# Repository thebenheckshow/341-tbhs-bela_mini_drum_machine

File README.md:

# 341-tbhs-bela_mini_drum_machine
In this episode Felix creates a drum machine with the Pocket Beagle and Bela Mini!!!!

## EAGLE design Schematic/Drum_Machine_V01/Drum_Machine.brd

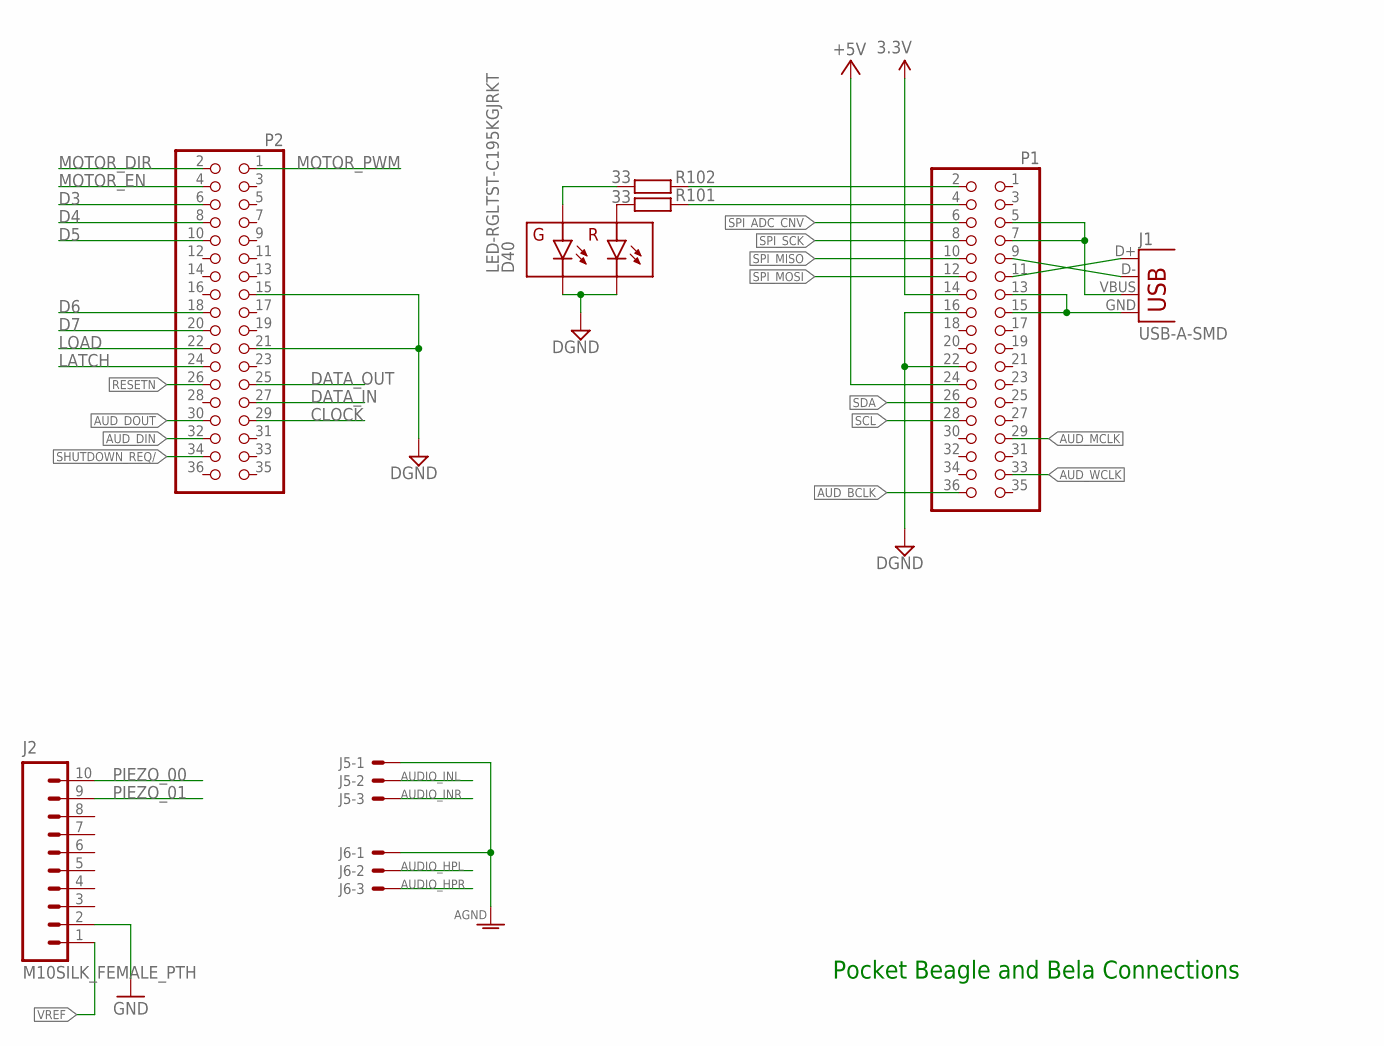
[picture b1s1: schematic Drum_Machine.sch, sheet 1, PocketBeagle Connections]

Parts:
D40: LED-RGLTST-C195KGJRKT; LTST-C195KGJRKT
J1: USB-A-SMD; USB-A-S-NOSILK-FEMALE
J2: M10SILK_FEMALE_PTH; 1X10
J5, J6: 22-23-2031
P1, P2: PINHD-2X18; 2X18
R101, R102: 33; R0603

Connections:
3.3V: P1.14; also elsewhere on the board
+5V_SYS: P1.24
AUDIO_HPL: J6.2
AUDIO_HPR: J6.3
AUDIO_INL: J5.2
AUDIO_INR: J5.3
AUD_BCLK: P1.36
AUD_DIN: P2.32
AUD_DOUT: P2.30
AUD_MCLK: P1.29
AUD_WCLK: P1.33
CLOCK: P2.29; also elsewhere on the board
D3: P2.6
D4: P2.8
D5: P2.10
D6: P2.18
D7: P2.20
DATA_IN: P2.27
DATA_OUT: P2.25; also elsewhere on the board
GND: D40.P$3 (GC), D40.P$4 (RC), J2.2, J5.1, J6.1, P1.16, P1.22, P2.15, P2.21; also elsewhere on the board
LATCH: P2.24; also elsewhere on the board
LOAD: P2.22
MOTOR_DIR: P2.2
MOTOR_EN: P2.4
MOTOR_PWM: P2.1
unnamed: D40.P$2 (RA), R101.2
unnamed: D40.P$1 (GA), R102.2
unnamed: P1.4, R101.1
unnamed: P1.2, R102.1
PIEZO_00: J2.10; also elsewhere on the board
PIEZO_01: J2.9; also elsewhere on the board
RESETN: P2.26
SCL: P1.28
SDA: P1.26
SHUTDOWN_REQ/: P2.34
SPI_ADC_CNV: P1.6
SPI_MISO: P1.10
SPI_MOSI: P1.12
SPI_SCK: P1.8
USBGND1: J1.GND, P1.13, P1.15
USB_DM1: J1.D-, P1.9
USB_DP1: J1.D+, P1.11
USB_VBUS1: J1.VBUS, P1.5, P1.7
VREF: J2.1; also elsewhere on the board

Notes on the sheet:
Pocket Beagle and Bela Connections

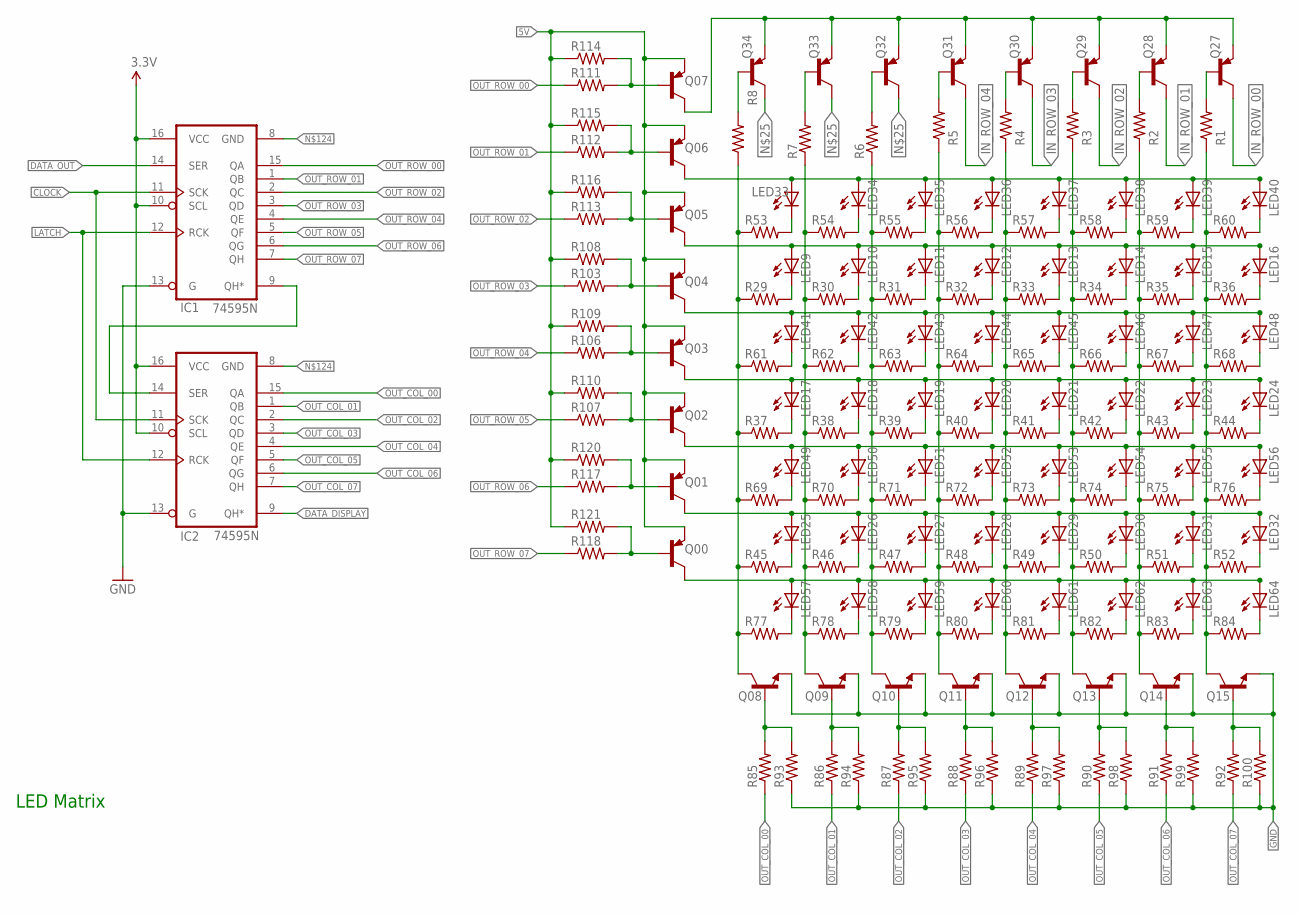
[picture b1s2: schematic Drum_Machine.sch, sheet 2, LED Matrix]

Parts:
IC1, IC2: 74595N; DIL16
LED9, LED10, LED11, LED12, LED13, LED14, LED15, LED16, LED17, LED18, LED19, LED20, LED21, LED22, LED23, LED24, LED25, LED26, LED27, LED28, LED29, LED30, LED31, LED32, LED33, LED34, LED35, LED36, LED37, LED38, LED39, LED40, LED41, LED42, LED43, LED44, LED45, LED46, LED47, LED48, LED49, LED50, LED51, LED52, LED53, LED54, LED55, LED56, LED57, LED58, LED59, LED60, LED61, LED62, LED63, LED64: LED5MM
Q00, Q01, Q02, Q03, Q04, Q05, Q06, Q07, Q27, Q28, Q29, Q30, Q31, Q32, Q33, Q34: BC857CSMD; SOT23-BEC
Q08, Q09, Q10, Q11, Q12, Q13, Q14, Q15: 2N4401-NPN-TO92-EBC; TO92-EBC
R1, R2, R3, R4, R5, R6, R7, R8, R29, R30, R31, R32, R33, R34, R35, R36, R37, R38, R39, R40, R41, R42, R43, R44, R45, R46, R47, R48, R49, R50, R51, R52, R53, R54, R55, R56, R57, R58, R59, R60, R61, R62, R63, R64, R65, R66, R67, R68, R69, R70, R71, R72, R73, R74, R75, R76, R77, R78, R79, R80, R81, R82, R83, R84, R85, R86, R87, R88, R89, R90, R91, R92, R93, R94, R95, R96, R97, R98, R99, R100, R103, R106, R107, R108, R109, R110, R111, R112, R113, R114, R115, R116, R117, R118, R120, R121: R-US_0309/10; 0309/10

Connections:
3.3V: IC1.10 (SCL), IC1.16 (VCC), IC2.10 (SCL), IC2.16 (VCC); also elsewhere on the board
5V: Q00.E, Q01.E, Q02.E, Q03.E, Q04.E, Q05.E, Q06.E, Q07.E, R108.1, R109.1, R110.1, R114.1, R115.1, R116.1, R120.1, R121.1; also elsewhere on the board
4445: Q06.B, R112.2, R115.2
CLOCK: IC1.11 (SCK), IC2.11 (SCK); also elsewhere on the board
DATA_DISPLAY: IC2.9 (QH*); also elsewhere on the board
DATA_OUT: IC1.14 (SER); also elsewhere on the board
GND: IC1.13 (G), IC2.13 (G), Q08.E, Q09.E, Q10.E, Q11.E, Q12.E, Q13.E, Q14.E, Q15.E, R93.1, R94.1, R95.1, R96.1, R97.1, R98.1, R99.1, R100.1; also elsewhere on the board
IN_ROW_00: Q27.C; also elsewhere on the board
IN_ROW_01: Q28.C; also elsewhere on the board
IN_ROW_02: Q29.C; also elsewhere on the board
IN_ROW_03: Q30.C; also elsewhere on the board
IN_ROW_04: Q31.C; also elsewhere on the board
LATCH: IC1.12 (RCK), IC2.12 (RCK); also elsewhere on the board
unnamed: Q27.B, R1.2
unnamed: Q07.C, Q27.E, Q28.E, Q29.E, Q30.E, Q31.E, Q32.E, Q33.E, Q34.E
unnamed: Q28.B, R2.2
unnamed: Q32.C, Q33.C, Q34.C
unnamed: Q29.B, R3.2
unnamed: Q30.B, R4.2
unnamed: Q31.B, R5.2
unnamed: Q32.B, R6.2
unnamed: Q33.B, R7.2
unnamed: LED9.A, LED10.A, LED11.A, LED12.A, LED13.A, LED14.A, LED15.A, LED16.A, Q05.C
unnamed: Q34.B, R8.2
unnamed: LED9.K (C), R29.2
unnamed: LED10.K (C), R30.2
unnamed: LED11.K (C), R31.2
unnamed: LED12.K (C), R32.2
unnamed: LED13.K (C), R33.2
unnamed: LED14.K (C), R34.2
unnamed: LED15.K (C), R35.2
unnamed: LED16.K (C), R36.2
unnamed: LED17.A, LED18.A, LED19.A, LED20.A, LED21.A, LED22.A, LED23.A, LED24.A, Q03.C
unnamed: LED17.K (C), R37.2
unnamed: LED18.K (C), R38.2
unnamed: LED19.K (C), R39.2
unnamed: LED20.K (C), R40.2
unnamed: LED21.K (C), R41.2
unnamed: LED22.K (C), R42.2
unnamed: LED23.K (C), R43.2
unnamed: LED24.K (C), R44.2
unnamed: LED25.A, LED26.A, LED27.A, LED28.A, LED29.A, LED30.A, LED31.A, LED32.A, Q01.C
unnamed: LED25.K (C), R45.2
unnamed: LED26.K (C), R46.2
unnamed: LED27.K (C), R47.2
unnamed: LED28.K (C), R48.2
unnamed: LED29.K (C), R49.2
unnamed: LED30.K (C), R50.2
unnamed: LED31.K (C), R51.2
unnamed: LED32.K (C), R52.2
unnamed: LED33.A, LED34.A, LED35.A, LED36.A, LED37.A, LED38.A, LED39.A, LED40.A, Q06.C
unnamed: LED33.K (C), R53.2
unnamed: LED34.K (C), R54.2
unnamed: LED35.K (C), R55.2
unnamed: LED36.K (C), R56.2
unnamed: LED37.K (C), R57.2
unnamed: LED38.K (C), R58.2
unnamed: LED39.K (C), R59.2
unnamed: LED40.K (C), R60.2
unnamed: LED41.A, LED42.A, LED43.A, LED44.A, LED45.A, LED46.A, LED47.A, LED48.A, Q04.C
unnamed: LED41.K (C), R61.2
unnamed: LED42.K (C), R62.2
unnamed: LED43.K (C), R63.2
unnamed: LED44.K (C), R64.2
unnamed: LED45.K (C), R65.2
unnamed: LED46.K (C), R66.2
unnamed: LED47.K (C), R67.2
unnamed: LED48.K (C), R68.2
unnamed: LED49.A, LED50.A, LED51.A, LED52.A, LED53.A, LED54.A, LED55.A, LED56.A, Q02.C
unnamed: LED49.K (C), R69.2
unnamed: LED50.K (C), R70.2
unnamed: LED51.K (C), R71.2
unnamed: LED52.K (C), R72.2
unnamed: LED53.K (C), R73.2
unnamed: LED54.K (C), R74.2
unnamed: LED55.K (C), R75.2
unnamed: LED56.K (C), R76.2
unnamed: LED57.A, LED58.A, LED59.A, LED60.A, LED61.A, LED62.A, LED63.A, LED64.A, Q00.C
unnamed: LED57.K (C), R77.2
unnamed: LED58.K (C), R78.2
unnamed: LED59.K (C), R79.2
unnamed: LED60.K (C), R80.2
unnamed: LED61.K (C), R81.2
unnamed: LED62.K (C), R82.2
unnamed: LED63.K (C), R83.2
unnamed: LED64.K (C), R84.2
unnamed: Q08.C, R8.1, R29.1, R37.1, R45.1, R53.1, R61.1, R69.1, R77.1
unnamed: Q09.C, R7.1, R30.1, R38.1, R46.1, R54.1, R62.1, R70.1, R78.1
unnamed: Q10.C, R6.1, R31.1, R39.1, R47.1, R55.1, R63.1, R71.1, R79.1
unnamed: Q11.C, R5.1, R32.1, R40.1, R48.1, R56.1, R64.1, R72.1, R80.1
unnamed: Q12.C, R4.1, R33.1, R41.1, R49.1, R57.1, R65.1, R73.1, R81.1
unnamed: Q13.C, R3.1, R34.1, R42.1, R50.1, R58.1, R66.1, R74.1, R82.1
unnamed: Q14.C, R2.1, R35.1, R43.1, R51.1, R59.1, R67.1, R75.1, R83.1
unnamed: Q15.C, R1.1, R36.1, R44.1, R52.1, R60.1, R68.1, R76.1, R84.1
unnamed: Q08.B, R85.2, R93.2
unnamed: IC1.8 (GND), IC2.8 (GND)
unnamed: Q09.B, R86.2, R94.2
unnamed: Q10.B, R87.2, R95.2
unnamed: Q11.B, R88.2, R96.2
unnamed: Q12.B, R89.2, R97.2
unnamed: Q13.B, R90.2, R98.2
unnamed: Q14.B, R91.2, R99.2
unnamed: Q15.B, R92.2, R100.2
unnamed: IC1.9 (QH*), IC2.14 (SER)
unnamed: Q04.B, R103.2, R108.2
unnamed: Q03.B, R106.2, R109.2
unnamed: Q02.B, R107.2, R110.2
unnamed: Q07.B, R111.2, R114.2
unnamed: Q05.B, R113.2, R116.2
unnamed: Q01.B, R117.2, R120.2
unnamed: Q00.B, R118.2, R121.2
OUT_COL_00: IC2.15 (QA), R85.1
OUT_COL_01: IC2.1 (QB), R86.1
OUT_COL_02: IC2.2 (QC), R87.1
OUT_COL_03: IC2.3 (QD), R88.1
OUT_COL_04: IC2.4 (QE), R89.1
OUT_COL_05: IC2.5 (QF), R90.1
OUT_COL_06: IC2.6 (QG), R91.1
OUT_COL_07: IC2.7 (QH), R92.1
OUT_ROW_00: IC1.15 (QA), R111.1
OUT_ROW_01: IC1.1 (QB), R112.1
OUT_ROW_02: IC1.2 (QC), R113.1
OUT_ROW_03: IC1.3 (QD), R103.1
OUT_ROW_04: IC1.4 (QE), R106.1
OUT_ROW_05: IC1.5 (QF), R107.1
OUT_ROW_06: IC1.6 (QG), R117.1
OUT_ROW_07: IC1.7 (QH), R118.1

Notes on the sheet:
LED Matrix

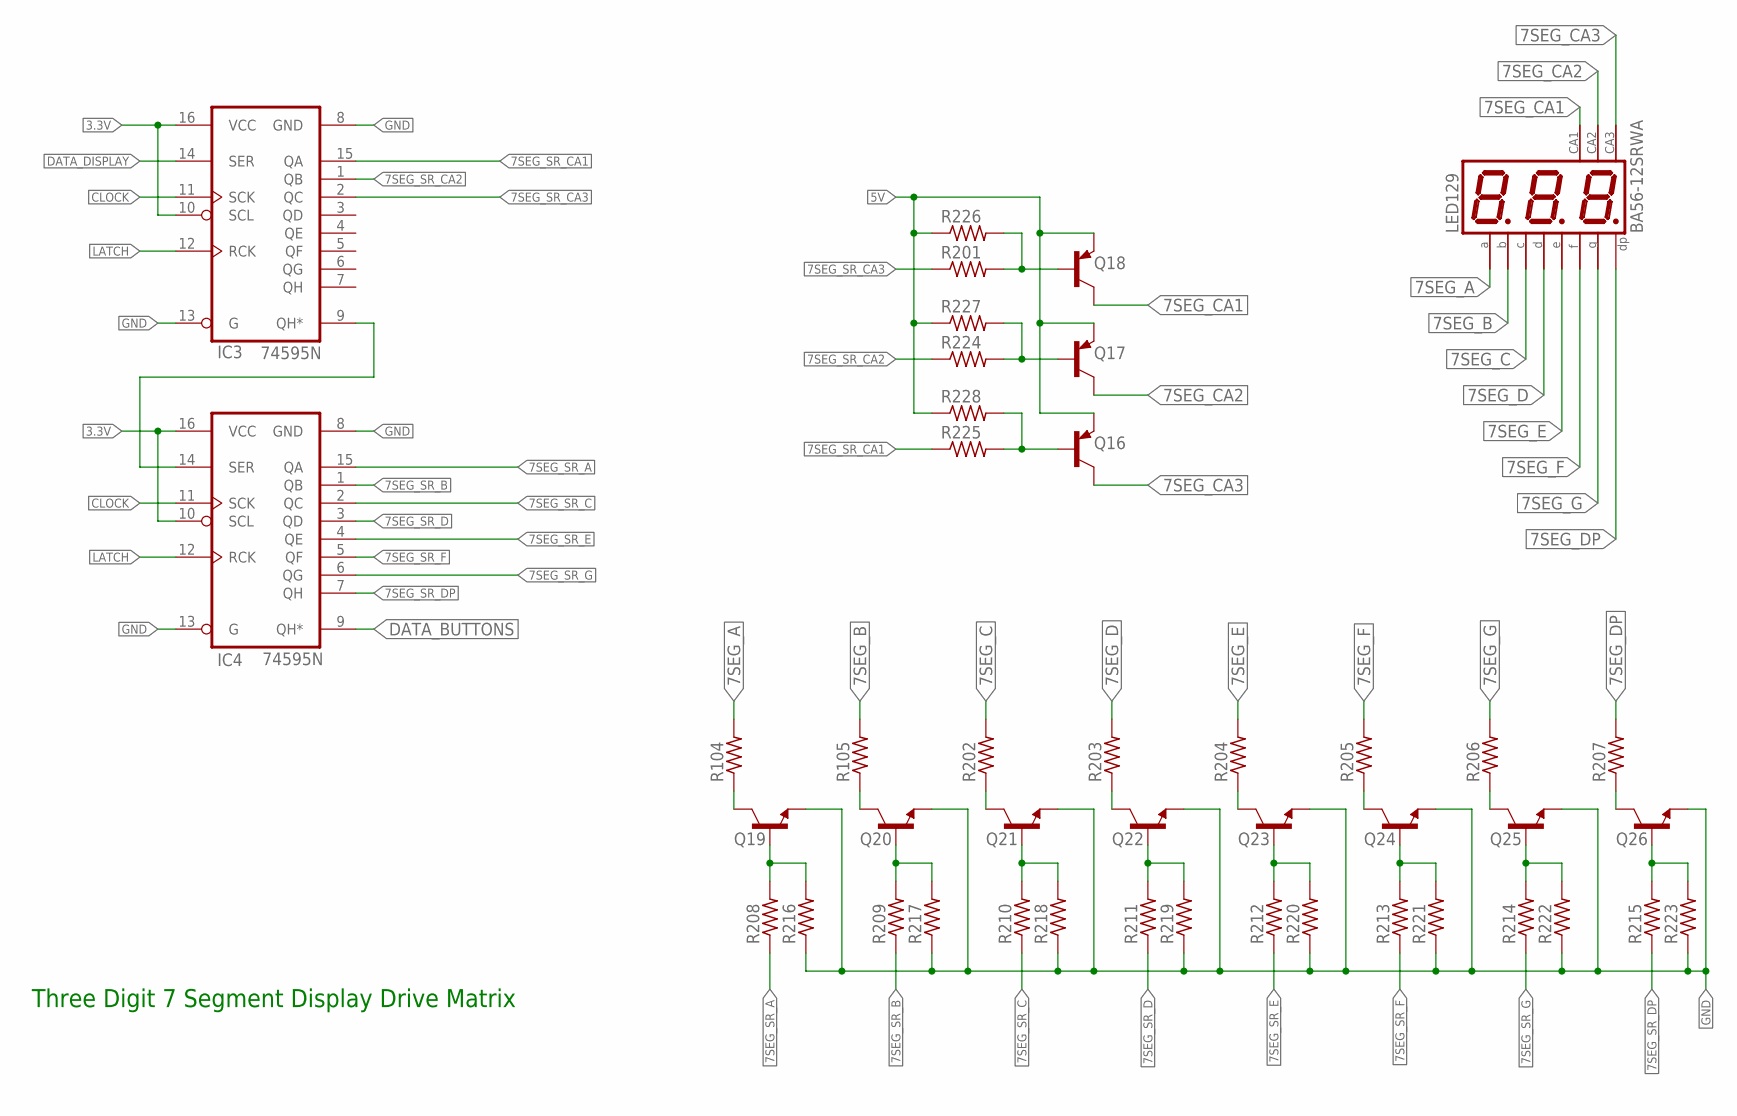
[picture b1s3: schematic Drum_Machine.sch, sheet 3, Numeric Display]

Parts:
IC3, IC4: 74595N; DIL16
LED129: BA56-12SRWA; BX56-12
Q16, Q17, Q18: BC857CSMD; SOT23-BEC
Q19, Q20, Q21, Q22, Q23, Q24, Q25, Q26: 2N4401-NPN-TO92-EBC; TO92-EBC
R104, R105, R201, R202, R203, R204, R205, R206, R207, R208, R209, R210, R211, R212, R213, R214, R215, R216, R217, R218, R219, R220, R221, R222, R223, R224, R225, R226, R227, R228: R-US_0309/10; 0309/10

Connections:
3.3V: IC3.10 (SCL), IC3.16 (VCC), IC4.10 (SCL), IC4.16 (VCC); also elsewhere on the board
5V: Q16.E, Q17.E, Q18.E, R226.1, R227.1, R228.1; also elsewhere on the board
7SEG_A: LED129.11 (A), R104.2
7SEG_B: LED129.7 (B), R105.2
7SEG_C: LED129.4 (C), R202.2
7SEG_CA1: LED129.12 (CA), Q18.C
7SEG_CA2: LED129.9 (CA), Q17.C
7SEG_CA3: LED129.8 (CA), Q16.C
7SEG_D: LED129.2 (D), R203.2
7SEG_DP: LED129.3 (DP), R207.2
7SEG_E: LED129.1 (E), R204.2
7SEG_F: LED129.10 (F), R205.2
7SEG_G: LED129.5 (G), R206.2
7SEG_SR_A: IC4.15 (QA), R208.1
7SEG_SR_B: IC4.1 (QB), R209.1
7SEG_SR_C: IC4.2 (QC), R210.1
7SEG_SR_CA1: IC3.15 (QA), R225.1
7SEG_SR_CA2: IC3.1 (QB), R224.1
7SEG_SR_CA3: IC3.2 (QC), R201.1
7SEG_SR_D: IC4.3 (QD), R211.1
7SEG_SR_DP: IC4.7 (QH), R215.1
7SEG_SR_E: IC4.4 (QE), R212.1
7SEG_SR_F: IC4.5 (QF), R213.1
7SEG_SR_G: IC4.6 (QG), R214.1
CLOCK: IC3.11 (SCK), IC4.11 (SCK); also elsewhere on the board
DATA_BUTTONS: IC4.9 (QH*)
DATA_DISPLAY: IC3.14 (SER); also elsewhere on the board
GND: IC3.8 (GND), IC3.13 (G), IC4.8 (GND), IC4.13 (G), Q19.E, Q20.E, Q21.E, Q22.E, Q23.E, Q24.E, Q25.E, Q26.E, R216.1, R217.1, R218.1, R219.1, R220.1, R221.1, R222.1, R223.1; also elsewhere on the board
LATCH: IC3.12 (RCK), IC4.12 (RCK); also elsewhere on the board
unnamed: IC3.9 (QH*), IC4.14 (SER)
unnamed: Q18.B, R201.2, R226.2
unnamed: Q19.C, R104.1
unnamed: Q20.C, R105.1
unnamed: Q21.C, R202.1
unnamed: Q22.C, R203.1
unnamed: Q23.C, R204.1
unnamed: Q24.C, R205.1
unnamed: Q25.C, R206.1
unnamed: Q26.C, R207.1
unnamed: Q19.B, R208.2, R216.2
unnamed: Q20.B, R209.2, R217.2
unnamed: Q21.B, R210.2, R218.2
unnamed: Q22.B, R211.2, R219.2
unnamed: Q23.B, R212.2, R220.2
unnamed: Q24.B, R213.2, R221.2
unnamed: Q25.B, R214.2, R222.2
unnamed: Q26.B, R215.2, R223.2
unnamed: Q17.B, R224.2, R227.2
unnamed: Q16.B, R225.2, R228.2

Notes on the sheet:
Three Digit 7 Segment Display Drive Matrix

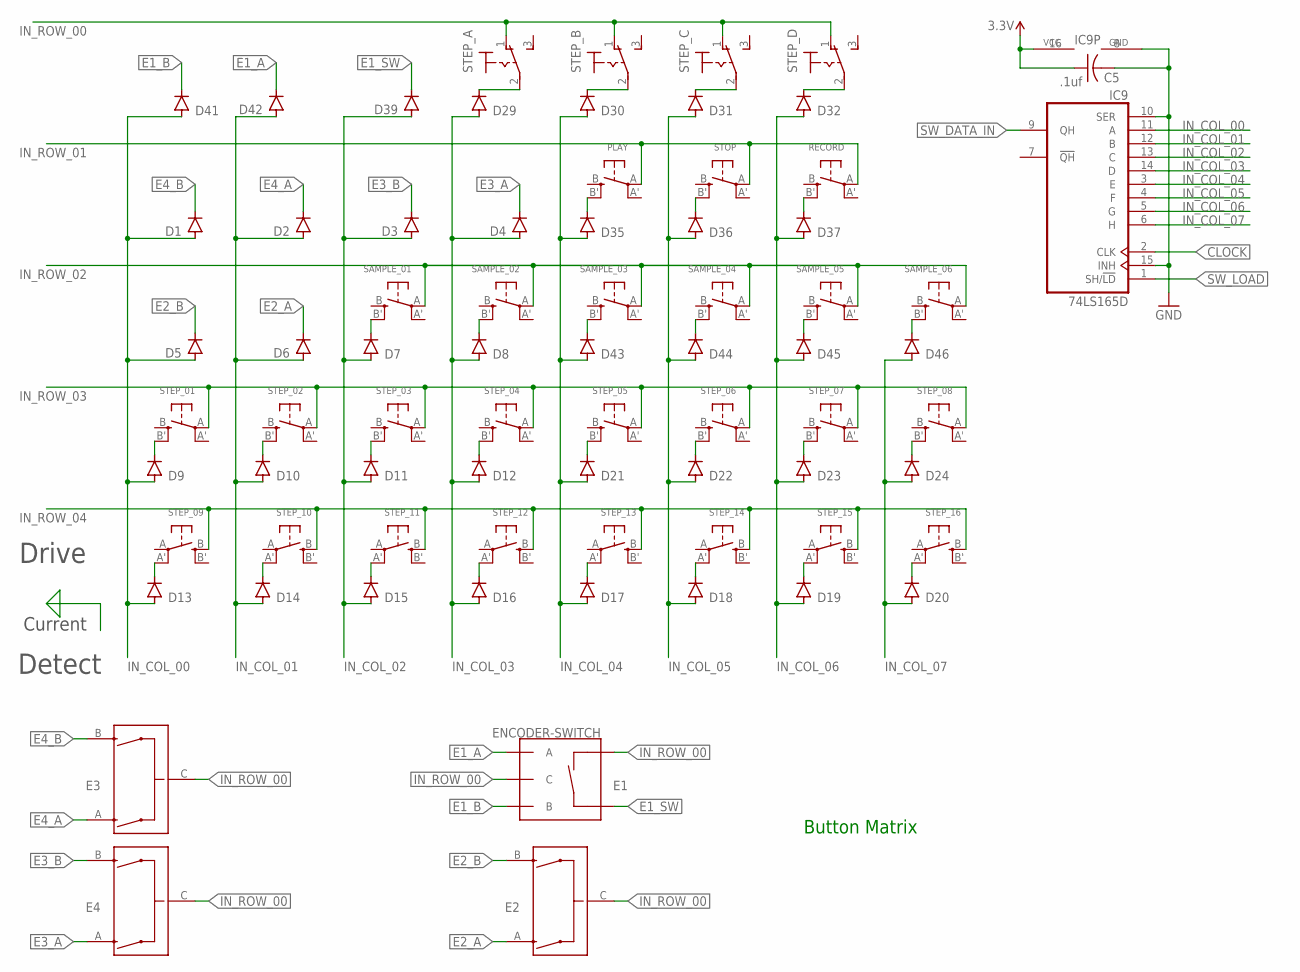
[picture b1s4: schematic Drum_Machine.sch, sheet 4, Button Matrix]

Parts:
C5: .1uf; C0805
D1, D2, D3, D4, D5, D6, D7, D8, D9, D10, D11, D12, D13, D14, D15, D16, D17, D18, D19, D20, D21, D22, D23, D24, D29, D30, D31, D32, D35, D36, D37, D39, D41, D42, D43, D44, D45, D46: PMLL4150; SOD80C@1
E1: ENCODER-SWITCH; ROTARY_ENC_PLAIN
E2, E3, E4: ENCODER; ENCODER-16MM-QUAD
IC9: 74LS165D; SO16
PLAY: SWITCH_TACT_SMT; EVQ-Q2
RECORD: SWITCH_TACT_SMT; EVQ-Q2
SAMPLE_01, SAMPLE_02, SAMPLE_03, SAMPLE_04, SAMPLE_05, SAMPLE_06: SWITCH_TACT_SMT; EVQ-Q2
STEP_01, STEP_02, STEP_03, STEP_04, STEP_05, STEP_06, STEP_07, STEP_08, STEP_09, STEP_10, STEP_11, STEP_12, STEP_13, STEP_14, STEP_15, STEP_16: SWITCH_TACT_SMT; EVQ-Q2
STEP_A: 320-916
STEP_B: 320-916
STEP_C: 320-916
STEP_D: 320-916
STOP: SWITCH_TACT_SMT; EVQ-Q2

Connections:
3.3V: C5.1, IC9.16 (VCC); also elsewhere on the board
CLOCK: IC9.2 (CLK); also elsewhere on the board
E1_A: D42.C, E1.A
E1_B: D41.C, E1.B
E1_SW: D39.C, E1.SW+
E2_A: D6.C, E2.A
E2_B: D5.C, E2.B
E3_A: D4.C, E4.A
E3_B: D3.C, E4.B
E4_A: D2.C, E3.A
E4_B: D1.C, E3.B
GND: C5.2, IC9.8 (GND), IC9.10 (SER), IC9.15 (INH); also elsewhere on the board
IN_COL_00: D1.A, D5.A, D9.A, D13.A, D41.A, IC9.11 (A)
IN_COL_01: D2.A, D6.A, D10.A, D14.A, D42.A, IC9.12 (B)
IN_COL_02: D3.A, D7.A, D11.A, D15.A, D39.A, IC9.13 (C)
IN_COL_03: D4.A, D8.A, D12.A, D16.A, D29.A, IC9.14 (D)
IN_COL_04: D17.A, D21.A, D30.A, D35.A, D43.A, IC9.3 (E)
IN_COL_05: D18.A, D22.A, D31.A, D36.A, D44.A, IC9.4 (F)
IN_COL_06: D19.A, D23.A, D32.A, D37.A, D45.A, IC9.5 (G)
IN_COL_07: D20.A, D24.A, D46.A, IC9.6 (H)
IN_ROW_00: E1.C, E1.SW-, E2.C, E3.C, E4.C, STEP_A.1 (O), STEP_B.1 (O), STEP_C.1 (O), STEP_D.1 (O); also elsewhere on the board
IN_ROW_01: PLAY.A, RECORD.A, STOP.A; also elsewhere on the board
IN_ROW_02: SAMPLE_01.A, SAMPLE_02.A, SAMPLE_03.A, SAMPLE_04.A, SAMPLE_05.A, SAMPLE_06.A; also elsewhere on the board
IN_ROW_03: STEP_01.A, STEP_02.A, STEP_03.A, STEP_04.A, STEP_05.A, STEP_06.A, STEP_07.A, STEP_08.A; also elsewhere on the board
IN_ROW_04: STEP_09.B (S), STEP_10.B (S), STEP_11.B (S), STEP_12.B (S), STEP_13.B (S), STEP_14.B (S), STEP_15.B (S), STEP_16.B (S); also elsewhere on the board
unnamed: D29.C, STEP_A.2
unnamed: D16.C, STEP_12.A' (P1)
unnamed: D17.C, STEP_13.A' (P1)
unnamed: D18.C, STEP_14.A' (P1)
unnamed: D15.C, STEP_11.A' (P1)
unnamed: D14.C, STEP_10.A' (P1)
unnamed: D13.C, STEP_09.A' (P1)
unnamed: D19.C, STEP_15.A' (P1)
unnamed: D20.C, STEP_16.A' (P1)
unnamed: D30.C, STEP_B.2
unnamed: D9.C, STEP_01.B' (S1)
unnamed: D10.C, STEP_02.B' (S1)
unnamed: D11.C, STEP_03.B' (S1)
unnamed: D12.C, STEP_04.B' (S1)
unnamed: D21.C, STEP_05.B' (S1)
unnamed: D22.C, STEP_06.B' (S1)
unnamed: D23.C, STEP_07.B' (S1)
unnamed: D24.C, STEP_08.B' (S1)
unnamed: D31.C, STEP_C.2
unnamed: D32.C, STEP_D.2
unnamed: D35.C, PLAY.B' (S1)
unnamed: D37.C, RECORD.B' (S1)
unnamed: D36.C, STOP.B' (S1)
unnamed: D7.C, SAMPLE_01.B' (S1)
unnamed: D8.C, SAMPLE_02.B' (S1)
unnamed: D43.C, SAMPLE_03.B' (S1)
unnamed: D44.C, SAMPLE_04.B' (S1)
unnamed: D45.C, SAMPLE_05.B' (S1)
unnamed: D46.C, SAMPLE_06.B' (S1)
SW_DATA_IN: IC9.9 (QH)
SW_LOAD: IC9.1 (SH/!LD)

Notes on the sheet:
Drive
Detect
Current
Button Matrix

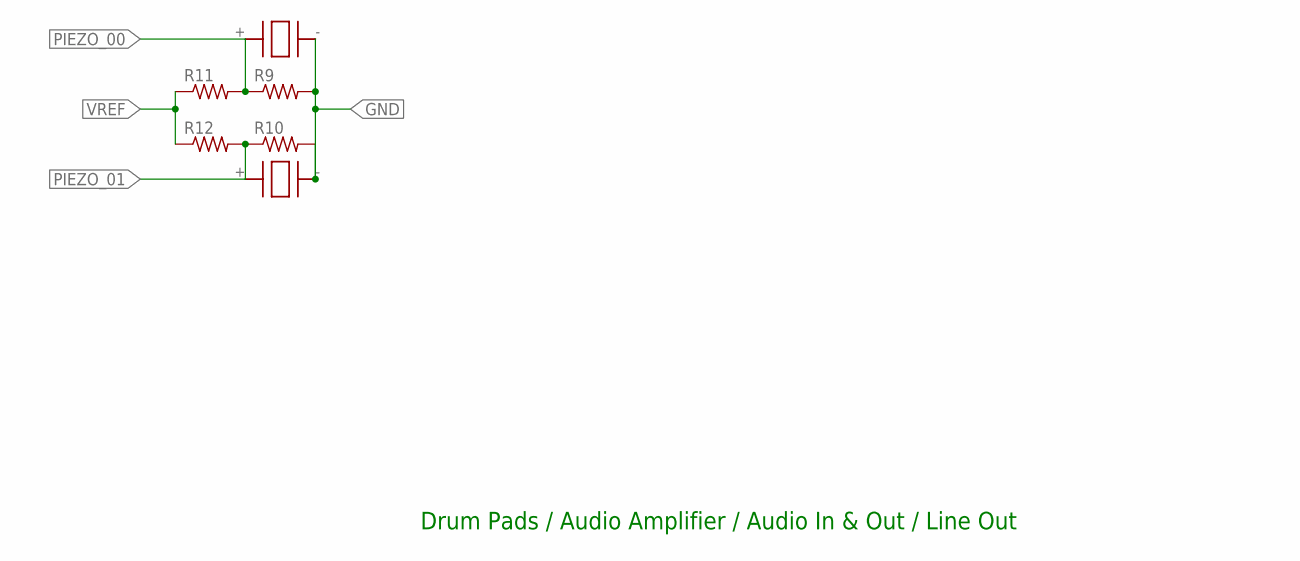
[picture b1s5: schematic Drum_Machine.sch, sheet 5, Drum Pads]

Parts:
R9, R10, R11, R12: R-US_0204/5; 0204/5
U$1, U$2: TRANSDUCER; DIAPHRAGM

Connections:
GND: R9.2, R10.2, U$1.-, U$2.-; also elsewhere on the board
PIEZO_00: R9.1, R11.2, U$2.+; also elsewhere on the board
PIEZO_01: R10.1, R12.2, U$1.+; also elsewhere on the board
VREF: R11.1, R12.1; also elsewhere on the board

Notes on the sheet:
Drum Pads / Audio Amplifier / Audio In & Out / Line Out

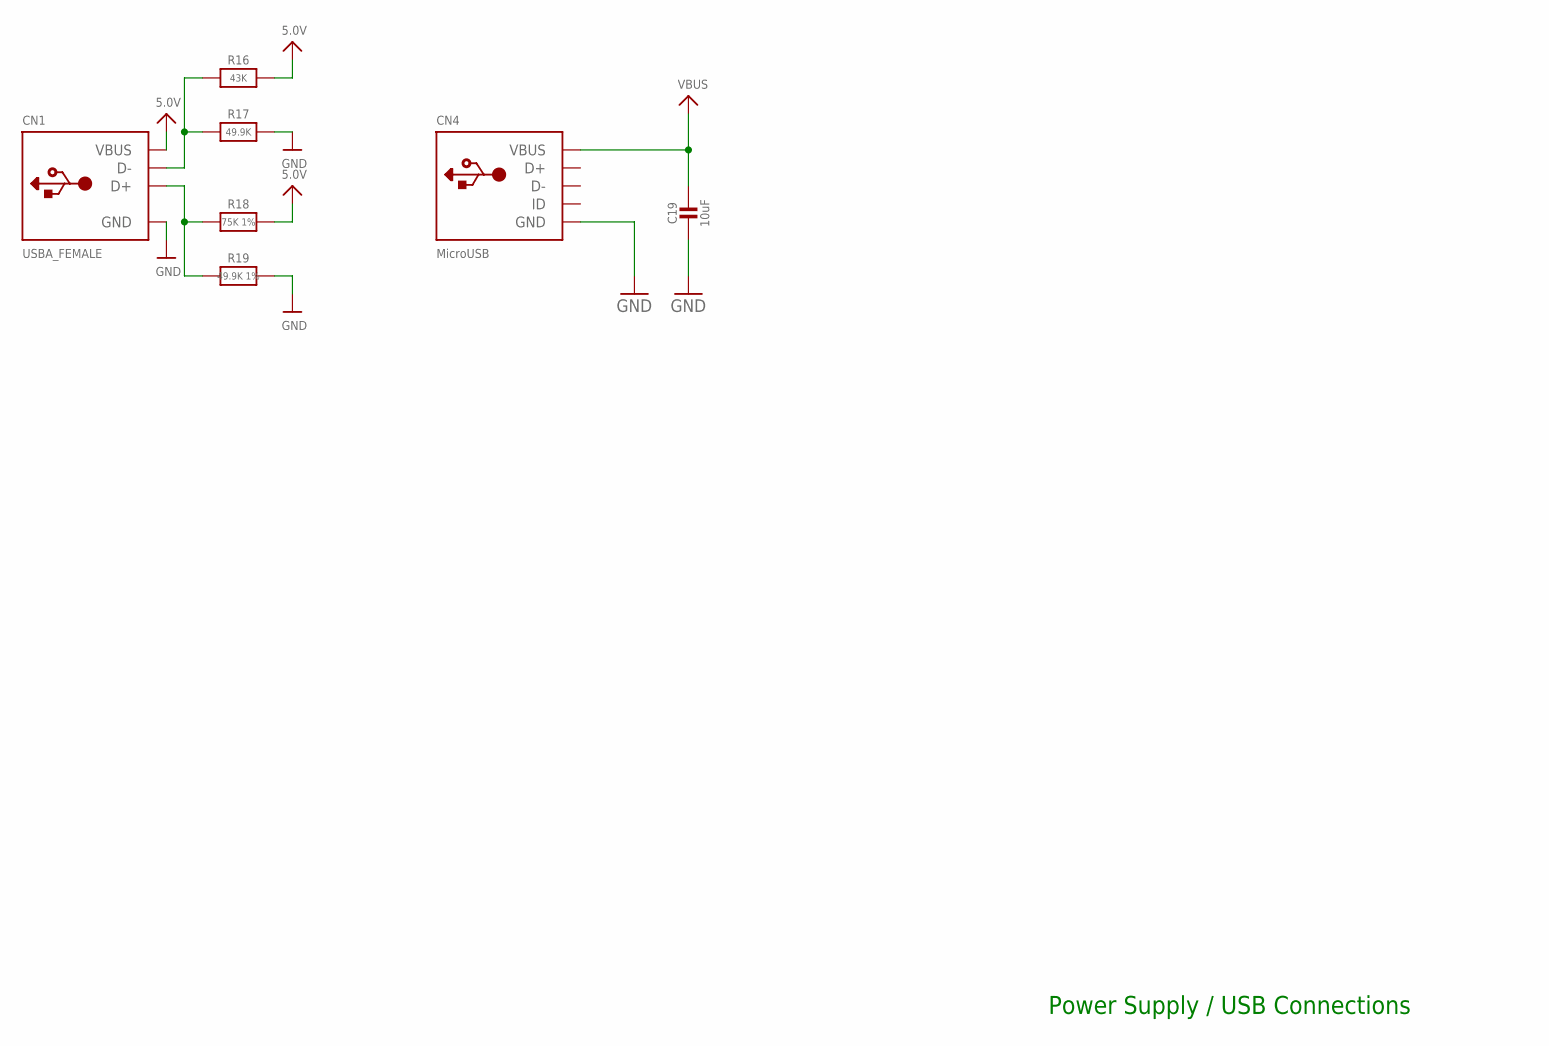
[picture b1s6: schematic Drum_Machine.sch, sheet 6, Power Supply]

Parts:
C19: 10uF; 0805-NO
CN1: USBA_FEMALE; USB_HOST-PTH
CN4: MicroUSB; 4UCONN_20329
R16: 43K; 0805-NO
R17: 49.9K; 0805-NO
R18: 75K 1%; 0805-NO
R19: 49.9K 1%; 0805-NO

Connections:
5.0V: CN1.VBUS, R16.2, R18.2
D+1: CN1.D+, R18.1, R19.1
D-1: CN1.D-, R16.1, R17.1
GND: C19.2, CN1.GND, CN4.BASE@1 (GND), CN4.BASE@2 (GND), CN4.GND, CN4.SPRT@1 (GND), CN4.SPRT@2 (GND), CN4.SPRT@3 (GND), CN4.SPRT@4 (GND), R17.2, R19.2; also elsewhere on the board
VBUS: C19.1, CN4.VBUS

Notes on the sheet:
Power Supply / USB Connections

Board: 2 copper layers, 323 parts (0 on the bottom side), 230 nets, no tracks yet.

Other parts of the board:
JP1: 1X08-3.5MM
JP2, JP3: 1X05/90
JP4: 2X05/90
JP5, JP6: 1X08/90

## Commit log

2018-04-26 Initial Commit - Upload Rough Schematic
2018-04-26 Updated connections
2018-04-26 Added enclosure and 3D files
2018-04-27 Added code development.
2018-04-29 Working SPI Example

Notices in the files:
parts and their libraries:
SparkFun-Switches: Licensing: Creative Commons ShareAlike 4.0 International - https://creativecommons.org/licenses/by-sa/4.0
SparkFun-Aesthetics: Licensing: CC v3.0 Share-Alike You are welcome to use this library for commercial purposes.
